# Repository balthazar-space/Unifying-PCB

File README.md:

# Balthazar

Open-hardware laptop computer modules description and concept.

These are electronic schematic modules as presented at https://balthazar.space/wiki/Balthazar with the main aim for team access. See the [main repository](https://github.com/balthazar-space/balthazar) for other designs.

# Unifying-PCB

Unifying PCB expansion for Balthazar 

Single PCB solution for connecting the three previously designed Balthazar modules (I/O, power supply, USB 2.0, 3.0 controllers, keyboard and adding Compute Module compatible FPGA boards. Aimed at setting a compatibility standard to widely accepted hardware standards.
It has standardized 100 pin accomodating module for adding standard CM HAT modules based on ARM or FPGA 
It has GPIO expansion port, HDMI,2x USB 3.0, Ethernet RJ45 and a microSD card slot.  

It is designed to accomodate ULX4M-CM4-HAT designed by Radiona.org using HDR 100 POS SMT board to board mezzanine connectors.

dimensions: 120x80 mm
placement: right back side of Balthazar casing

## License

All resources except the keyboard firmware - which is licensed with with GPLv3 or later - licensed under the CERN Open Hardware Licence CERN-OHL W V.2.0

Version 2.0 of the CERN-OHL introduces three variants of the licence – strongly (S) reciprocal, weakly (W) reciprocal and permissive (P) – which aim to address specific constraints caused by different collaboration models currently used in open-hardware projects. 

The first two variants mean that if any product is made using an open hardware design, the design of that product, including any improvements or modifications, should be made available under the same licence as that of the original product. Permissive licences do not impose this condition.

See the [LICENSE.md](./LICENSE.md) file for more information.

## Funding

This project is funded through the [NGI Zero Entrust Fund](https://nlnet.nl/entrust), a fund
established by [NLnet](https://nlnet.nl) with financial support from the European Commission's
[Next Generation Internet](https://ngi.eu) program. Learn more on the [NLnet project page](https://nlnet.nl/project/Balthazar-Casing/).

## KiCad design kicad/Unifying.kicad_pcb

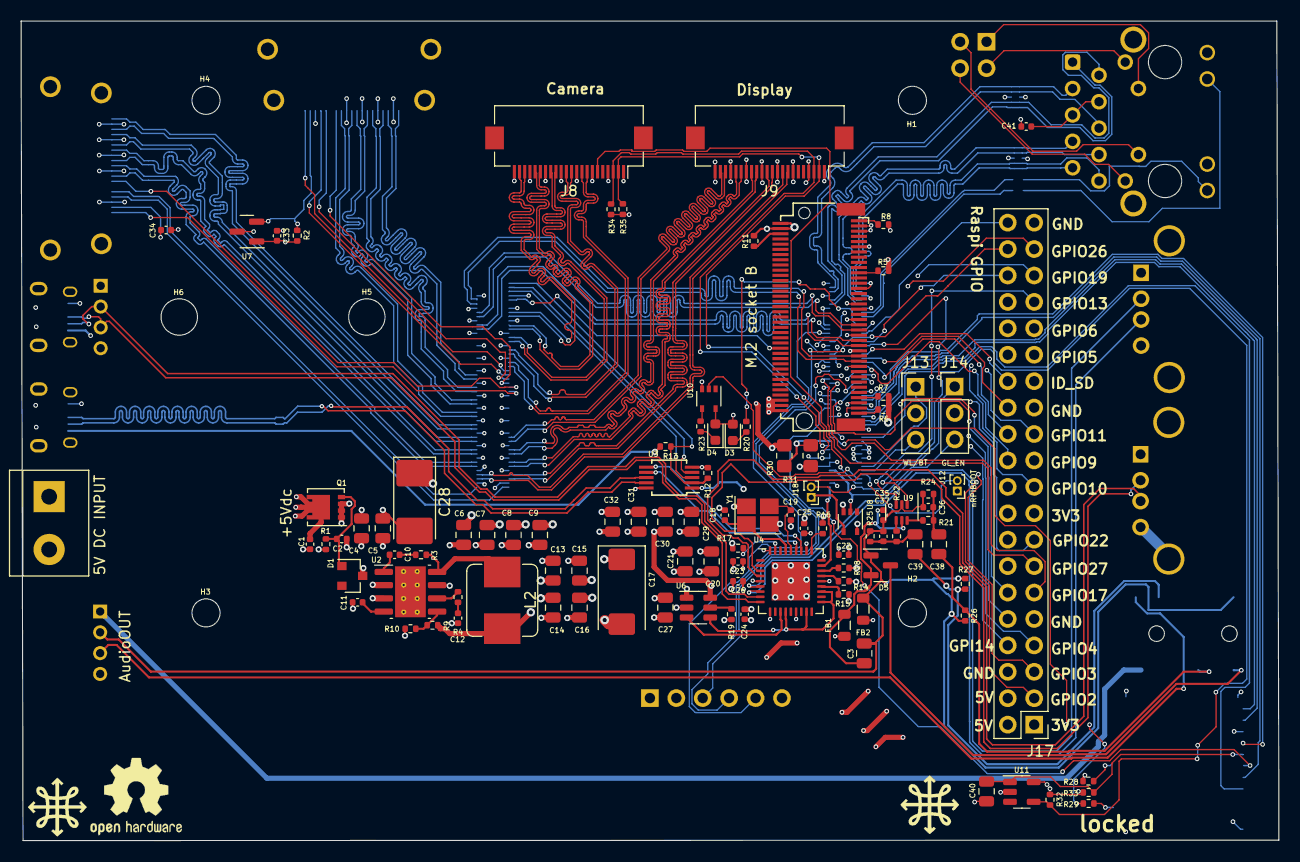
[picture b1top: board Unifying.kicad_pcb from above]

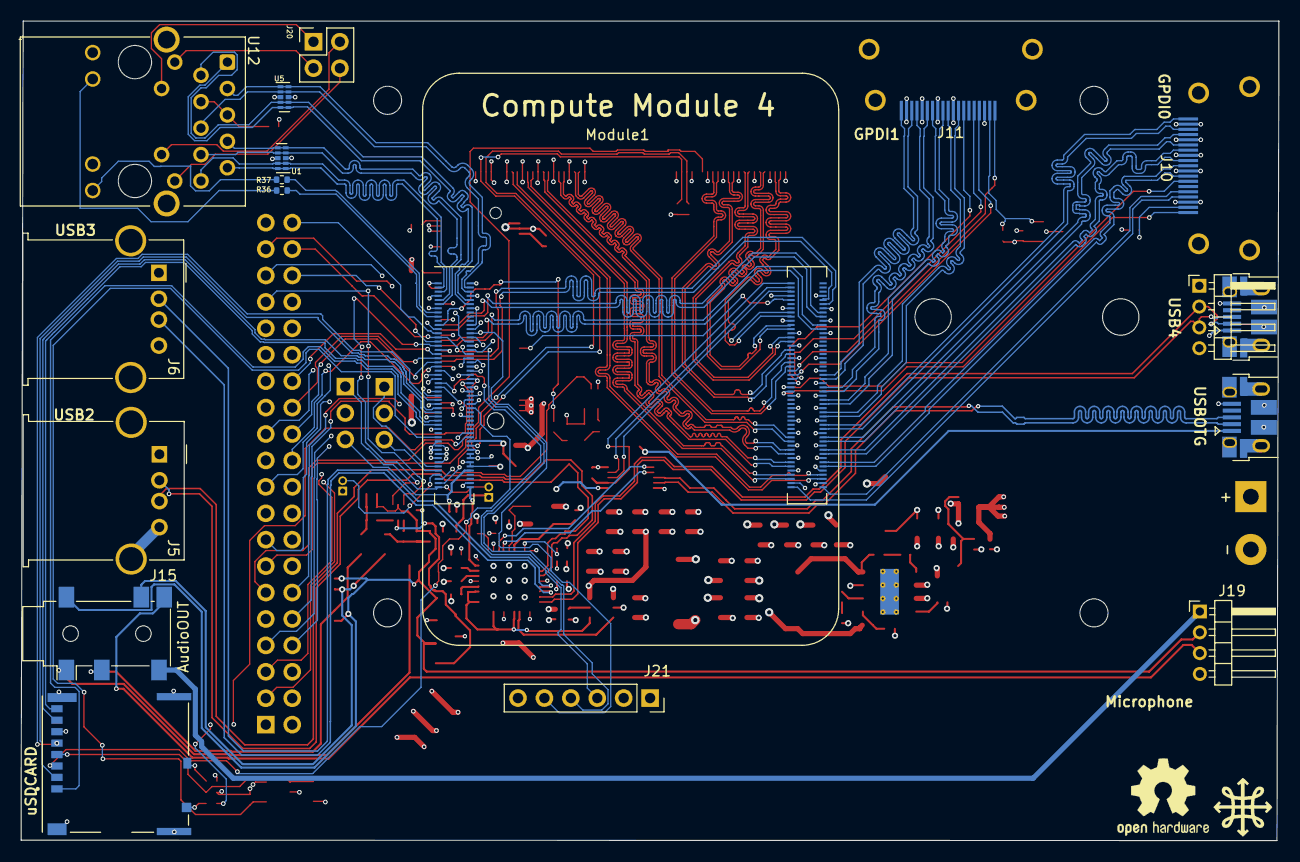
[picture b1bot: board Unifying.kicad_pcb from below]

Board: 4 copper layers, 120.9 x 78.8 mm, 127 parts (18 on the bottom side), 179 nets.

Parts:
C1: 100n 50v; C_0402_1005Metric
C2, C10, C11, C22, C23, C24, C25, C26, C33, C34, C41: 100n; C_0402_1005Metric
C3, C13, C14, C15, C16, C20, C21, C27, C29, C30, C31, C32, C40: 10u; C_0805_2012Metric
C4, C5, C6, C7, C8, C9: 10u 10v; C_0805_2012Metric
C12: 1.2nF; C_0402_1005Metric
C17: 100uF; CP_EIA-7343-31_Kemet-D
C18, C19: 27pF; C_0402_1005Metric
C28: 100uF; CP_EIA-7132-20_AVX-U
C35, C36, C37: 100n 6.3; C_0402_1005Metric
C38, C39: 47u 6.3; C_0805_2012Metric
D1: MMBZ5242BLT3G; D_SOT-23_ANK
D3: LED Green; LED_0603_1608Metric
D4: LED Red; LED_0603_1608Metric
D5: BAV99; SOT-23
FB1, FB2: FerriteBead; L_0805_2012Metric
H1, H2, H3, H4: MountingHole; MountingHole_2.7mm_M2.5
H5, H6: M.2 Hole; M.2Hole_3.5mm
J1: Conn_01x02; TerminalBlock_bornier-2_P5.08mm
J2: Bus_M.2_Socket_B; Conn_TE-M.2-0.5-67P-doublesided
J3: USB_OTG; USB_Micro-B_EDAC_UCON00686
J4: Conn_01x04_Male; PinHeader_1x04_P2.00mm_Horizontal
J5, J6: USB_A; USB_A_Molex_67643_Horizontal
J7: USB_MICRO; USB_Micro-B_EDAC_UCON00686
J8, J9: Conn_01x22_Female; Hirose_FH12-22S-0.5SH_1x22-1MP_P0.50mm_Horizontal
J10: GPDI0; CONN-10029449-111RLF
J11: GPDI1; CONN-10029449-111RLF
J12: nRpiBoot; PinHeader_1x02_P1.00mm_Vertical
J13, J14: Conn_01x03; PinHeader_1x03_P2.54mm_Vertical
J15: AudioOUT; Jack_3.5mm_PJ311_Horizontal
J16: Micro_SD_Card_Det; SDCARD_MOLEX_503398-1892
J17: THD-20-R; PinHeader_2x20_P2.54mm_Vertical
J18: GLOBAL_EN; PinHeader_1x02_P1.00mm_Vertical
J19: AudioAMP; PinHeader_1x04_P2.00mm_Horizontal
J20: THD-02-R; PinHeader_2x02_P2.54mm_Vertical
J21: MIC; PinSocket_1x06_P2.54mm_Vertical
L2: SRN6045TA-3R3Y (3.3uH); L_Bourns_SRP7028A_7.3x6.6mm
Module1: ComputeModule4; Raspberry-Pi-4-Compute-Module-noholes
Q1: DMP3013SFV-7; Diodes_PowerDI3333-8
R1, R4, R17, R32: 12K 1%; R_0402_1005Metric
R2, R33: DNP; R_0402_1005Metric
R3: 10R; R_0402_1005Metric
R5, R6, R7, R8, R28, R29: nf; R_0402_1005Metric
R9: 47K 1%; R_0402_1005Metric
R10, R19: 15K 1%; R_0402_1005Metric
R11: 12K; R_0402_1005Metric
R12, R13: 2.2K 1%; R_0402_1005Metric
R14, R15, R16, R18: 36K 1%; R_0402_1005Metric
R20, R23: 1k; R_0402_1005Metric
R21, R22: 220; R_0402_1005Metric
R24, R25: 100; R_0402_1005Metric
R26, R27: 1K8; R_0402_1005Metric
R30: 0R; R_0805_2012Metric_Pad1.20x1.40mm_HandSolder
R31: nf; R_0805_2012Metric_Pad1.20x1.40mm_HandSolder
R34, R35: 4K7; R_0402_1005Metric
R36, R37: 470R; R_0402_1005Metric
U1, U5: TPD4EUSB30; USON-10_2.5x1.0mm_P0.5mm
U2: AP64501SP-13; SOIC-8-1EP_3.9x4.9mm_P1.27mm_EP2.95x4.9mm_Mask2.71x3.4mm_Th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
U3: FSUSB42MUX; MSOP-10_3x3mm_P0.5mm
U4: USB2514B-I/M2; QFN-36-1EP_6x6mm_P0.5mm_EP3.7x3.7mm
U6: AP22653W6; SOT-23-6
U7: RT9742SNGV; SOT-23
U8, U10: 74LVC1G07SE-7; SOT-353_SC-70-5
U9: NC7WZ16; SC-88-6_2x2.1mm
U11: RT9742GGJ5; SOT-23-5
U12: MagJack-A70-112-331N126; TRJG0926HENL
Y1: 24MHz; Crystal_SMD_EuroQuartz_X22-4Pin_2.5x2.0mm_HandSoldering

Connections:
/+3.3v: C20.1, C21.1, C22.1, C23.1, C24.1, C25.1, C26.1, D3.2 (A), D4.2 (A), FB1.1, J8.1, J9.1, J17.1, J17.17, J21.1, Module1.84 (+3.3v_(Output)), Module1.86 (+3.3v_(Output)), R28.1, R30.1, R32.1, R33.2, R34.1, R35.1, U3.1 (VCC), U4.5 (VDDA33), U4.10 (VDDA33), U4.15 (VDD33), U4.23 (VDD33), U4.27 (VBUS_DET), U4.29 (VDDA33), U4.36 (VDDA33), U10.5 (VCC), U11.5 (IN), U12.15 (LEDG_A), U12.17 (LEDY_A)
/+3.3vSSD: C13.1, C14.1, C15.1, C16.1, C17.1, J2.2 (3.3V), J2.4 (3.3V), J2.70 (3.3V), J2.72 (3.3V), J2.74 (3.3V), L2.2, R5.1, R6.1, R7.1, R8.1, R9.1, R11.2
/+5v: C2.1, C4.1, C5.1, C6.1, C7.1, C8.1, C9.1, C27.1, C33.1, D1.1 (K), J17.2, J17.4, Module1.77 (+5v_(Input)), Module1.79 (+5v_(Input)), Module1.81 (+5v_(Input)), Module1.83 (+5v_(Input)), Module1.85 (+5v_(Input)), Module1.87 (+5v_(Input)), Q1.1 (S), Q1.2 (S), Q1.3 (S), R2.1, U2.2 (VIN), U2.3 (EN), U6.1 (IN), U7.1 (IN), U8.5 (VCC)
/CM4_GPIO (GPIO, SDCARD)/+1.8v: Module1.88 (+1.8v_(Output)), Module1.90 (+1.8v_(Output)), R31.1
/CM4_GPIO (GPIO, SDCARD)/AUDIO_L: C38.2, J15.3, R26.2
/CM4_GPIO (GPIO, SDCARD)/AUDIO_R: C39.2, J15.4, R27.2
/CM4_GPIO (GPIO, SDCARD)/BCLK: J17.12, J21.3, Module1.49 (GPIO18)
/CM4_GPIO (GPIO, SDCARD)/BT_nDis: J13.3, Module1.91 (BT_nDisable)
/CM4_GPIO (GPIO, SDCARD)/DOUT: J17.38, J21.4, Module1.27 (GPIO20)
/CM4_GPIO (GPIO, SDCARD)/ETH_LEDG: Module1.17 (Ethernet_nLED2(3.3v)), R36.2
/CM4_GPIO (GPIO, SDCARD)/ETH_LEDY: Module1.15 (Ethernet_nLED3(3.3v)), R37.2
/CM4_GPIO (GPIO, SDCARD)/GLOBAL_EN: J14.1, J18.2, Module1.99 (Global_EN)
/CM4_GPIO (GPIO, SDCARD)/GPIO2: J17.3, Module1.58 (GPIO2)
/CM4_GPIO (GPIO, SDCARD)/GPIO3: J17.5, Module1.56 (GPIO3)
/CM4_GPIO (GPIO, SDCARD)/GPIO4: J17.7, Module1.54 (GPIO4)
/CM4_GPIO (GPIO, SDCARD)/GPIO5: J17.29, Module1.34 (GPIO5)
/CM4_GPIO (GPIO, SDCARD)/GPIO6: J17.31, Module1.30 (GPIO6)
/CM4_GPIO (GPIO, SDCARD)/GPIO7: J17.26, Module1.37 (GPIO7)
/CM4_GPIO (GPIO, SDCARD)/GPIO8: J17.24, Module1.39 (GPIO8)
/CM4_GPIO (GPIO, SDCARD)/GPIO9: J17.21, Module1.40 (GPIO9)
/CM4_GPIO (GPIO, SDCARD)/GPIO10: J17.19, Module1.44 (GPIO10)
/CM4_GPIO (GPIO, SDCARD)/GPIO11: J17.23, Module1.38 (GPIO11)
/CM4_GPIO (GPIO, SDCARD)/GPIO12: J17.32, Module1.31 (GPIO12), U9.1 (A1)
/CM4_GPIO (GPIO, SDCARD)/GPIO13: J17.33, Module1.28 (GPIO13), U9.3 (A2)
/CM4_GPIO (GPIO, SDCARD)/GPIO14: J17.8, Module1.55 (GPIO14)
/CM4_GPIO (GPIO, SDCARD)/GPIO15: J17.10, Module1.51 (GPIO15)
/CM4_GPIO (GPIO, SDCARD)/GPIO16: J17.36, Module1.29 (GPIO16)
/CM4_GPIO (GPIO, SDCARD)/GPIO17: J17.11, Module1.50 (GPIO17)
/CM4_GPIO (GPIO, SDCARD)/GPIO21: J17.40, Module1.25 (GPIO21)
/CM4_GPIO (GPIO, SDCARD)/GPIO22: J17.15, Module1.46 (GPIO22)
/CM4_GPIO (GPIO, SDCARD)/GPIO23: J17.16, Module1.47 (GPIO23)
/CM4_GPIO (GPIO, SDCARD)/GPIO24: J17.18, Module1.45 (GPIO24)
/CM4_GPIO (GPIO, SDCARD)/GPIO25: J17.22, Module1.41 (GPIO25)
/CM4_GPIO (GPIO, SDCARD)/GPIO26: J17.37, Module1.24 (GPIO26)
/CM4_GPIO (GPIO, SDCARD)/GPIO27: J17.13, Module1.48 (GPIO27)
/CM4_GPIO (GPIO, SDCARD)/GPIO_VREF: Module1.78 (GPIO_VREF(1.8v/3.3v_Input)), R30.2, R31.2
/CM4_GPIO (GPIO, SDCARD)/ID_SC: J17.28, Module1.35 (ID_SC)
/CM4_GPIO (GPIO, SDCARD)/ID_SD: J17.27, Module1.36 (ID_SD)
/CM4_GPIO (GPIO, SDCARD)/LRCL: J17.35, J21.5, Module1.26 (GPIO19)
/CM4_GPIO (GPIO, SDCARD)/RUN_PG: J14.3, Module1.92 (RUN_PG), U8.2
/CM4_GPIO (GPIO, SDCARD)/Reserved: Module1.76 (Reserved), R29.1
/CM4_GPIO (GPIO, SDCARD)/SD_CLK: J16.5 (CLK), Module1.57 (SD_CLK)
/CM4_GPIO (GPIO, SDCARD)/SD_CMD: J16.3 (CMD), Module1.62 (SD_CMD)
/CM4_GPIO (GPIO, SDCARD)/SD_DAT0: J16.7 (DAT0), Module1.63 (SD_DAT0)
/CM4_GPIO (GPIO, SDCARD)/SD_DAT1: J16.8 (DAT1), Module1.67 (SD_DAT1)
/CM4_GPIO (GPIO, SDCARD)/SD_DAT2: J16.1 (DAT2), Module1.69 (SD_DAT2)
/CM4_GPIO (GPIO, SDCARD)/SD_DAT3: J16.2 (DAT3/CD), Module1.61 (SD_DAT3)
/CM4_GPIO (GPIO, SDCARD)/SD_PWR: C40.1, J16.4 (VDD), R33.1, U11.1 (OUT)
/CM4_GPIO (GPIO, SDCARD)/SD_PWR_ON: Module1.75 (SD_PWR_ON), R32.2, U11.4 (EN)
/CM4_GPIO (GPIO, SDCARD)/TR0_TAP: J20.3, U12.11 (VC1)
/CM4_GPIO (GPIO, SDCARD)/TR1_TAP: J20.1, U12.12 (VC2)
/CM4_GPIO (GPIO, SDCARD)/TR2_TAP: J20.2, U12.13 (VC3)
/CM4_GPIO (GPIO, SDCARD)/TR3_TAP: J20.4, U12.14 (VC4)
/CM4_GPIO (GPIO, SDCARD)/TRD0_N: Module1.10 (Ethernet_Pair0_N), U5.4 (D2+), U5.7, U12.2 (TRD0-)
/CM4_GPIO (GPIO, SDCARD)/TRD0_P: Module1.12 (Ethernet_Pair0_P), U5.5 (D2-), U5.6, U12.1 (TRD0+)
/CM4_GPIO (GPIO, SDCARD)/TRD1_N: Module1.6 (Ethernet_Pair1_N), U5.2 (D1-), U5.9, U12.6 (TRD1-)
/CM4_GPIO (GPIO, SDCARD)/TRD1_P: Module1.4 (Ethernet_Pair1_P), U5.1 (D1+), U5.10, U12.3 (TRD1+)
/CM4_GPIO (GPIO, SDCARD)/TRD2_N: Module1.9 (Ethernet_Pair2_N), U1.4 (D2+), U1.7, U12.8 (TRD2-)
/CM4_GPIO (GPIO, SDCARD)/TRD2_P: Module1.11 (Ethernet_Pair2_P), U1.5 (D2-), U1.6, U12.7 (TRD2+)
/CM4_GPIO (GPIO, SDCARD)/TRD3_N: Module1.5 (Ethernet_Pair3_N), U1.2 (D1-), U1.9, U12.10 (TRD3-)
/CM4_GPIO (GPIO, SDCARD)/TRD3_P: Module1.3 (Ethernet_Pair3_P), U1.1 (D1+), U1.10, U12.9 (TRD3+)
/CM4_GPIO (GPIO, SDCARD)/WL_nDis: J13.1, Module1.89 (WiFi_nDisable)
/CM4_GPIO (GPIO, SDCARD)/nPWR_LED: Module1.95 (nPI_LED_PWR), U10.2
/CM4_GPIO (GPIO, SDCARD)/nRPIBOOT: J12.2, Module1.93 (nRPIBOOT)
/CM4_HighSpeed/CAM1_C_N: J8.15, Module1.127 (CAM1_C_N)
/CM4_HighSpeed/CAM1_C_P: J8.14, Module1.129 (CAM1_C_P)
/CM4_HighSpeed/CAM1_D0_N: J8.21, Module1.115 (CAM1_D0_N)
/CM4_HighSpeed/CAM1_D0_P: J8.20, Module1.117 (CAM1_D0_P)
/CM4_HighSpeed/CAM1_D1_N: J8.18, Module1.121 (CAM1_D1_N)
/CM4_HighSpeed/CAM1_D1_P: J8.17, Module1.123 (CAM1_D1_P)
/CM4_HighSpeed/CAM1_D2_N: J8.12, Module1.133 (CAM1_D2_N)
/CM4_HighSpeed/CAM1_D2_P: J8.11, Module1.135 (CAM1_D2_P)
/CM4_HighSpeed/CAM1_D3_N: J8.9, Module1.139 (CAM1_D3_N)
/CM4_HighSpeed/CAM1_D3_P: J8.8, Module1.141 (CAM1_D3_P)
/CM4_HighSpeed/CAM_GPIO: J8.6, Module1.97 (Camera_GPIO)
/CM4_HighSpeed/DSI1_C_N: J9.15, Module1.187 (DSI1_C_N)
/CM4_HighSpeed/DSI1_C_P: J9.14, Module1.189 (DSI1_C_P)
/CM4_HighSpeed/DSI1_D0_N: J9.21, Module1.175 (DSI1_D0_N)
/CM4_HighSpeed/DSI1_D0_P: J9.20, Module1.177 (DSI1_D0_P)
/CM4_HighSpeed/DSI1_D1_N: J9.18, Module1.181 (DSI1_D1_N)
/CM4_HighSpeed/DSI1_D1_P: J9.17, Module1.183 (DSI1_D1_P)
/CM4_HighSpeed/DSI1_D2_N: J9.12, Module1.193 (DSI1_D2_N)
/CM4_HighSpeed/DSI1_D2_P: J9.11, Module1.195 (DSI1_D2_P)
/CM4_HighSpeed/DSI1_D3_N: J9.9, Module1.194 (DSI1_D3_N)
/CM4_HighSpeed/DSI1_D3_P: J9.8, Module1.196 (DSI1_D3_P)
/CM4_HighSpeed/HDMI1_CEC: J11.13, Module1.149 (HDMI1_CEC)
/CM4_HighSpeed/HDMI1_CK_N: J11.12, Module1.166 (HDMI1_CLK_N)
/CM4_HighSpeed/HDMI1_CK_P: J11.10, Module1.164 (HDMI1_CLK_P)
/CM4_HighSpeed/HDMI1_D0_N: J11.9, Module1.160 (HDMI1_TX0_N)
/CM4_HighSpeed/HDMI1_D0_P: J11.7, Module1.158 (HDMI1_TX0_P)
/CM4_HighSpeed/HDMI1_D1_N: J11.6, Module1.154 (HDMI1_TX1_N)
/CM4_HighSpeed/HDMI1_D1_P: J11.4, Module1.152 (HDMI1_TX1_P)
/CM4_HighSpeed/HDMI1_D2_N: J11.3, Module1.148 (HDMI1_TX2_N)
/CM4_HighSpeed/HDMI1_D2_P: J11.1, Module1.146 (HDMI1_TX2_P)
/CM4_HighSpeed/HDMI1_HOTPLUG: J11.19, Module1.143 (HDMI1_HOTPLUG)
/CM4_HighSpeed/HDMI1_SCL: J11.15, Module1.147 (HDMI1_SCL)
/CM4_HighSpeed/HDMI1_SDA: J11.16, Module1.145 (HDMI1_SDA)
/CM4_HighSpeed/SCL0: J8.3, J9.3, Module1.80 (SCL0), R34.2
/CM4_HighSpeed/SDA0: J8.2, J9.2, Module1.82 (SDA0), R35.2
/CM4_HighSpeed/USB2_N: Module1.103 (USB2_N), U3.4 (D_N)
/CM4_HighSpeed/USB2_P: Module1.105 (USB2_P), U3.3 (D_P)
/CM4_HighSpeed/USBOTG_ID: Module1.101 (USB_OTG_ID), R12.1, R13.2, U3.2 (SEL)
/PCIE_CLK_N: J2.53 (REFCLKn), Module1.112 (PCIe_CLK_N)
/PCIE_CLK_P: J2.55 (REFCLKp), Module1.110 (PCIe_CLK_P)
/PCIE_RX_N: J2.41 (PERn0/SATA-B+), Module1.118 (PCIe_RX_N)
/PCIE_RX_P: J2.43 (PERp0/SATA-B-), Module1.116 (PCIe_RX_P)
/PCIE_TX_N: J2.47 (PETn0/SATA-A-), Module1.124 (PCIe_TX_N)
/PCIE_TX_P: J2.49 (PETp0/SATA-A+), Module1.122 (PCIe_TX_P)
/PCIE_nRST: J2.50 (~PERST), Module1.109 (PCIe_nRST)
/USB2-HUB/HD2_N: J5.2 (D-), U4.3 (USBDM_DN2/PRT_DIS_M2)
/USB2-HUB/HD2_P: J5.3 (D+), U4.4 (USBDP_DN2/PRT_DIS_P2)
/USB2-HUB/HD3_N: J6.2 (D-), U4.6 (USBDM_DN3/PRT_DIS_M3)
/USB2-HUB/HD3_P: J6.3 (D+), U4.7 (USBDP_DN3/PRT_DIS_P3)
/USB2-HUB/HD4_N: J4.2, J7.2 (D-), U4.8 (USBDM_DN4/PRT_DIS_M4)
/USB2-HUB/HD4_P: J4.3, J7.3 (D+), U4.9 (USBDP_DN4/PRT_DIS_P4)
/USB2-HUB/PWR1: U4.12 (PRTPWR1/BC_EN1), U6.3 (EN)
/USB2-HUB/USBD_N: J3.2 (D-), U3.8 (HSD1_M)
/USB2-HUB/USBD_P: J3.3 (D+), U3.9 (HSD1_P)
/USB2-HUB/USBH_N: U3.6 (HSD0_M), U4.30 (USBDM_UP)
/USB2-HUB/USBH_P: U3.7 (HSD0_P), U4.31 (USBDP_UP)
/USB2-HUB/VBUS: C28.1, C29.1, C30.1, C31.1, C32.1, J4.1, J5.1 (VBUS), J6.1 (VBUS), J7.1 (VBUS), U6.6 (OUT)
/USB2-HUB/nOCS1: U4.13 (OCS_N1), U4.17 (OCS_N2), U4.19 (OCS_N3), U4.21 (OCS_N4), U6.4 (nFault)
/nEXTRST: Module1.100 (nEXTRST), U4.26 (RESET_N)
GND: C1.2, C4.2, C5.2, C6.2, C7.2, C8.2, C9.2, C11.2, C12.2, C13.2, C14.2, C15.2, C16.2, C17.2, C18.2, C19.2, C20.2, C21.2, C22.2, C23.2, C24.2, C25.2, C26.2, C27.2, C28.2, C29.2, C30.2, C31.2, C32.2, C33.2, C34.2, C40.2, C41.2, FB2.2, J1.2, J2.3 (GND), J2.5 (GND), J2.11 (GND), J2.27 (GND), J2.33 (GND), J2.39 (GND), J2.45 (GND), J2.51 (GND), J2.57 (GND), J2.71 (GND), J2.73 (GND), J3.5 (GND), J3.6 (Shield), J4.4, J5.4 (GND), J5.5 (Shield), J6.4 (GND), J6.5 (Shield), J7.5 (GND), J7.6 (Shield), J8.4, J8.7, J8.10, J8.13, J8.16, J8.19, J8.22, J9.4, J9.7, J9.10, J9.13, J9.16, J9.19, J9.22, J10.0, J10.2, J10.5, J10.8, J10.11, J10.17, J11.0, J11.2, J11.5, J11.8, J11.11, J11.17, J12.1, J13.2, J14.2, J16.6 (VSS), J16.11 (SHIELD), J17.6, J17.9, J17.14, J17.20, J17.25, J17.30, J17.34, J17.39, J21.2, J21.6, Module1.1 (GND), Module1.2 (GND), Module1.7 (GND), Module1.8 (GND), Module1.13 (GND), Module1.14 (GND), Module1.22 (GND), Module1.23 (GND), Module1.32 (GND), Module1.33 (GND), Module1.42 (GND), Module1.43 (GND), Module1.52 (GND), Module1.53 (GND), Module1.59 (GND), Module1.60 (GND), Module1.65 (GND), Module1.66 (GND), Module1.71 (GND), Module1.74 (GND), Module1.98 (GND), Module1.107 (GND), Module1.108 (GND), Module1.113 (GND), Module1.114 (GND), Module1.119 (GND), Module1.120 (GND), Module1.125 (GND), Module1.126 (GND), Module1.131 (GND), Module1.132 (GND), Module1.137 (GND), Module1.138 (GND), Module1.144 (GND), Module1.150 (GND), Module1.155 (GND), Module1.156 (GND), Module1.161 (GND), Module1.162 (GND), Module1.167 (GND), Module1.168 (GND), Module1.173 (GND), Module1.174 (GND), Module1.179 (GND), Module1.180 (GND), Module1.185 (GND), Module1.186 (GND), Module1.191 (GND), Module1.192 (GND), Module1.197 (GND), Module1.198 (GND), R1.2, R10.2, R12.2, R14.2, R15.2, R16.2, R17.1, R18.2, R19.2, U1.3 (GND), U1.8 (GND), U2.7 (GND), U2.9 (EP), U3.5 (GND), U3.10 (nOE), U4.37 (VSS), U5.3 (GND), U5.8 (GND), U6.2 (GND), U7.3 (GND), U8.3 (GND), U10.3 (GND), U11.2 (GND), U12.19 (SHIELD), U12.20 (SHIELD), Y1.2, Y1.4
HDMI0_CEC: J10.13, Module1.151 (HDMI0_CEC)
HDMI0_CK_N: J10.12, Module1.190 (HDMI0_CLK_N)
HDMI0_CK_P: J10.10, Module1.188 (HDMI0_CLK_P)
HDMI0_D0_N: J10.9, Module1.184 (HDMI0_TX0_N)
HDMI0_D0_P: J10.7, Module1.182 (HDMI0_TX0_P)
HDMI0_D1_N: J10.6, Module1.178 (HDMI0_TX1_N)
HDMI0_D1_P: J10.4, Module1.176 (HDMI0_TX1_P)
HDMI0_D2_N: J10.3, Module1.172 (HDMI0_TX2_N)
HDMI0_D2_P: J10.1, Module1.170 (HDMI0_TX2_P)
HDMI0_HOTPLUG: J10.19, Module1.153 (HDMI0_HOTPLUG)
HDMI0_SCL: J10.15, Module1.200 (HDMI0_SCL)
HDMI0_SDA: J10.16, Module1.199 (HDMI0_SDA)
HDMI_5v: C34.1, J10.18, J11.18, R2.2, U7.2 (OUT)
unnamed: C10.1, R3.2
unnamed: C12.1, R4.2
unnamed: C36.1, C38.1, R21.2, R24.2
unnamed: C37.1, C39.1, R22.2, R25.2
unnamed: C2.2, D1.2 (A), Q1.4 (G), R1.1
unnamed: D3.1 (K), R20.1
unnamed: D4.1 (K), R23.1
unnamed: C3.1, C35.1, D5.2 (A), FB1.2, U9.5 (Vcc)
unnamed: D5.3 (K), J15.1
unnamed: C3.2, C35.2, C36.2, C37.2, D5.1 (K), FB2.1, J15.2, J19.2, R24.1, R25.1, R26.1, R27.1, U9.2 (GND)
unnamed: C1.1, J1.1, Q1.5 (D)
unnamed: J2.21 (CONFIG_0), R5.2
unnamed: J2.69 (CONFIG_1), R6.2
unnamed: J2.75 (CONFIG_2), R7.2
unnamed: J2.1 (CONFIG_3), R8.2
unnamed: J2.6 (~FULL_CARD_POWER_OFF), R11.1
unnamed: J3.1 (VBUS), R13.1
unnamed: J16.10 (DET_A), R28.2
unnamed: J16.9 (DET_B), R29.2
unnamed: J18.1, U8.4
unnamed: J15.6, J19.1
unnamed: J15.5, J19.3
unnamed: Module1.21 (PI_nLED_Activity), R20.2
unnamed: R23.2, U10.4
unnamed: C10.2, U2.1 (BST)
unnamed: R4.1, U2.6 (COMP)
unnamed: R9.2, R10.1, U2.5 (FB)
unnamed: C11.1, U2.4 (SS)
unnamed: L2.1, R3.1, U2.8 (SW)
unnamed: R18.1, U4.25 (HS_IND/CFG_SEL1)
unnamed: R17.2, U4.35 (RBIAS)
unnamed: R14.1, U4.24 (SCL/SMBCLK/CFG_SEL0)
unnamed: R15.1, U4.22 (SDA/SMBDATA/NON_REM1)
unnamed: R16.1, U4.28 (SUSP_IND/LOCAL_PWR/NON_REM0)
unnamed: C18.1, U4.33 (XTALIN/CLKIN), Y1.1
unnamed: C19.1, U4.32 (XTALOUT), Y1.3
unnamed: R19.1, U6.5 (ILIM)
unnamed: R21.1, U9.6 (Y1)
unnamed: R22.1, U9.4 (Y2)
unnamed: C41.1, U12.4 (CT), U12.5 (CT)
unnamed: R36.1, U12.16 (LEDG_K)
unnamed: R37.1, U12.18 (LEDY_K)

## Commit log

2022-03-28 Initial routing of high speed signals
2022-03-28 Aditional routing
2022-04-04 Adding normal size HDMI connectors
2022-04-04 Adding 3D modesl
2022-04-04 Routing High speed signals
2022-04-04 Routing SD
2022-04-04 Partialy routing GPIO
2022-04-05 All wires connected
2022-04-05 Completed initial routing
2022-04-06 Tuning differential signals
2022-04-06 Removing U1
2022-04-06 Changing L2
2022-04-06 Fixing errors, fixing most warnings
2022-04-06 Adding GlobalENable, and RpiBoot
2022-04-11 Adding audio connector - fixing USB, adding logos
2022-04-11 Directory structure change
2022-04-11 Renaming to Unifying
2022-04-11 Removing logo
2022-04-11 New pictures
2022-04-15 Adding power layer filled zones
2022-04-15 Adding test production file
2022-05-25 Fixing remaining errors
2022-06-08 Adding interactive BOM
2022-06-29 Adding latest version
2022-06-29 Adding kitspace files
2022-06-29 Moving gerber files
2022-07-10 Update part list
2022-10-05 Mirroring CAM, DSI, new GPDI pinout fix #2 #3 #5 #12
2022-10-05 Adding changes to PCB, routing board
2022-10-06 Adding I2C poullups to schematics
2022-10-06 Adding I2C resistors on PCB - routing fix 4
2022-10-06 Adding ethernet connector to schematics
2022-10-06 Adding I2S MIC connector
2022-10-06 Cleaning all errors
2022-10-06 Initial routing of ethernet fix #13
2022-10-06 Adding MIC connector fix #14
2022-10-06 Routing GPIOs
2022-10-07 Rounting all signals fix #16
2022-10-07 Adding new BOM - fix #8
2022-10-07 Slightly improving routing
2022-10-07 Adding/moving some text fix #19
2022-10-07 Adding dimensions
2022-10-07 README update
2022-10-07 Tuning diff pair
2022-10-07 Tune skew - fix #17
2022-10-07 Connecting MIC fix #20
2022-10-07 Adding v02 production files
2024-10-17 Adding datasheet fix #21
